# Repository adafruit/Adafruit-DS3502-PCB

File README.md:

## Adafruit DS3502 I2C Digital 10K Potentiometer  PCB

<a href="http://www.adafruit.com/products/4286"><br/>
Click here to purchase one from the Adafruit shop</a>

PCB files for the Adafruit DS3502 I2C Digital 10K Potentiometer . 

Format is EagleCAD schematic and board layout
* https://www.adafruit.com/product/4286

### Description

If you're a person like me that gets exhausted turning knobs all day, the DS3502 is just the ticket to calm all your knob-turning related troubles. Instead of having to _turn knobs_ with your _HANDS_ like an _ANIMAL_ the DS3502 I2C Digital Potentiometer allows you to let your microcontroller adjust the resistance for you! Now you can free your hands to spin your fidget spinner or or eat a slice of pizza while you're on the phone. Talking over an I2C bus, your Arduino, CircuitPython board,  or Python powered computer can talk to the DS3502 and tell it to vary its resistance at your beck and call.

Working with the DS3502 is easy as an I2C controllable pie. We've  put it on a breakout PCB with the required support circuitry and [SparkFun qwiic](https://www.sparkfun.com/qwiic) compatible [STEMMA QT](https://learn.adafruit.com/introducing-adafruit-stemma-qt) connectors to allow you to use it with other similarly equipped boards **without needing to solder.** This handy little helper can work with 3.3V or 5V micros, so it's ready to get to work with a range of development boards. The DS3502 is a simple chip that does one thing well and so it's very easy to work with. Wire it up and set the value for the wiper, thats it. [To make things _even easier_ we've gone and written Arduino and CircuitPython/Python 3 drivers to simplify interfacing with your new knob-replacing friend.](https://learn.adafruit.com/ds3502-i2c-potentiometer/)

"OK, this thing sounds great. Give me some details" you say. OK then, here you go: The wiper value is a 7-bit number meaning there are **128** possible levels of resistance to choose, from **0-10K ohms.** You can even set a default value that will be set on power up. The analog voltage controlled can be from **4.5-15.5V**. Additionally you can use the address jumpers or pins to set the I2C address to one of four values, allowing you to have four DS3502s on the same I2C bus.

### License

Adafruit invests time and resources providing this open source design, please support Adafruit and open-source hardware by purchasing products from [Adafruit](https://www.adafruit.com)!

Designed by Kattni Rembor for Adafruit Industries.

Creative Commons Attribution/Share-Alike, all text above must be included in any redistribution. 
See license.txt for additional details.

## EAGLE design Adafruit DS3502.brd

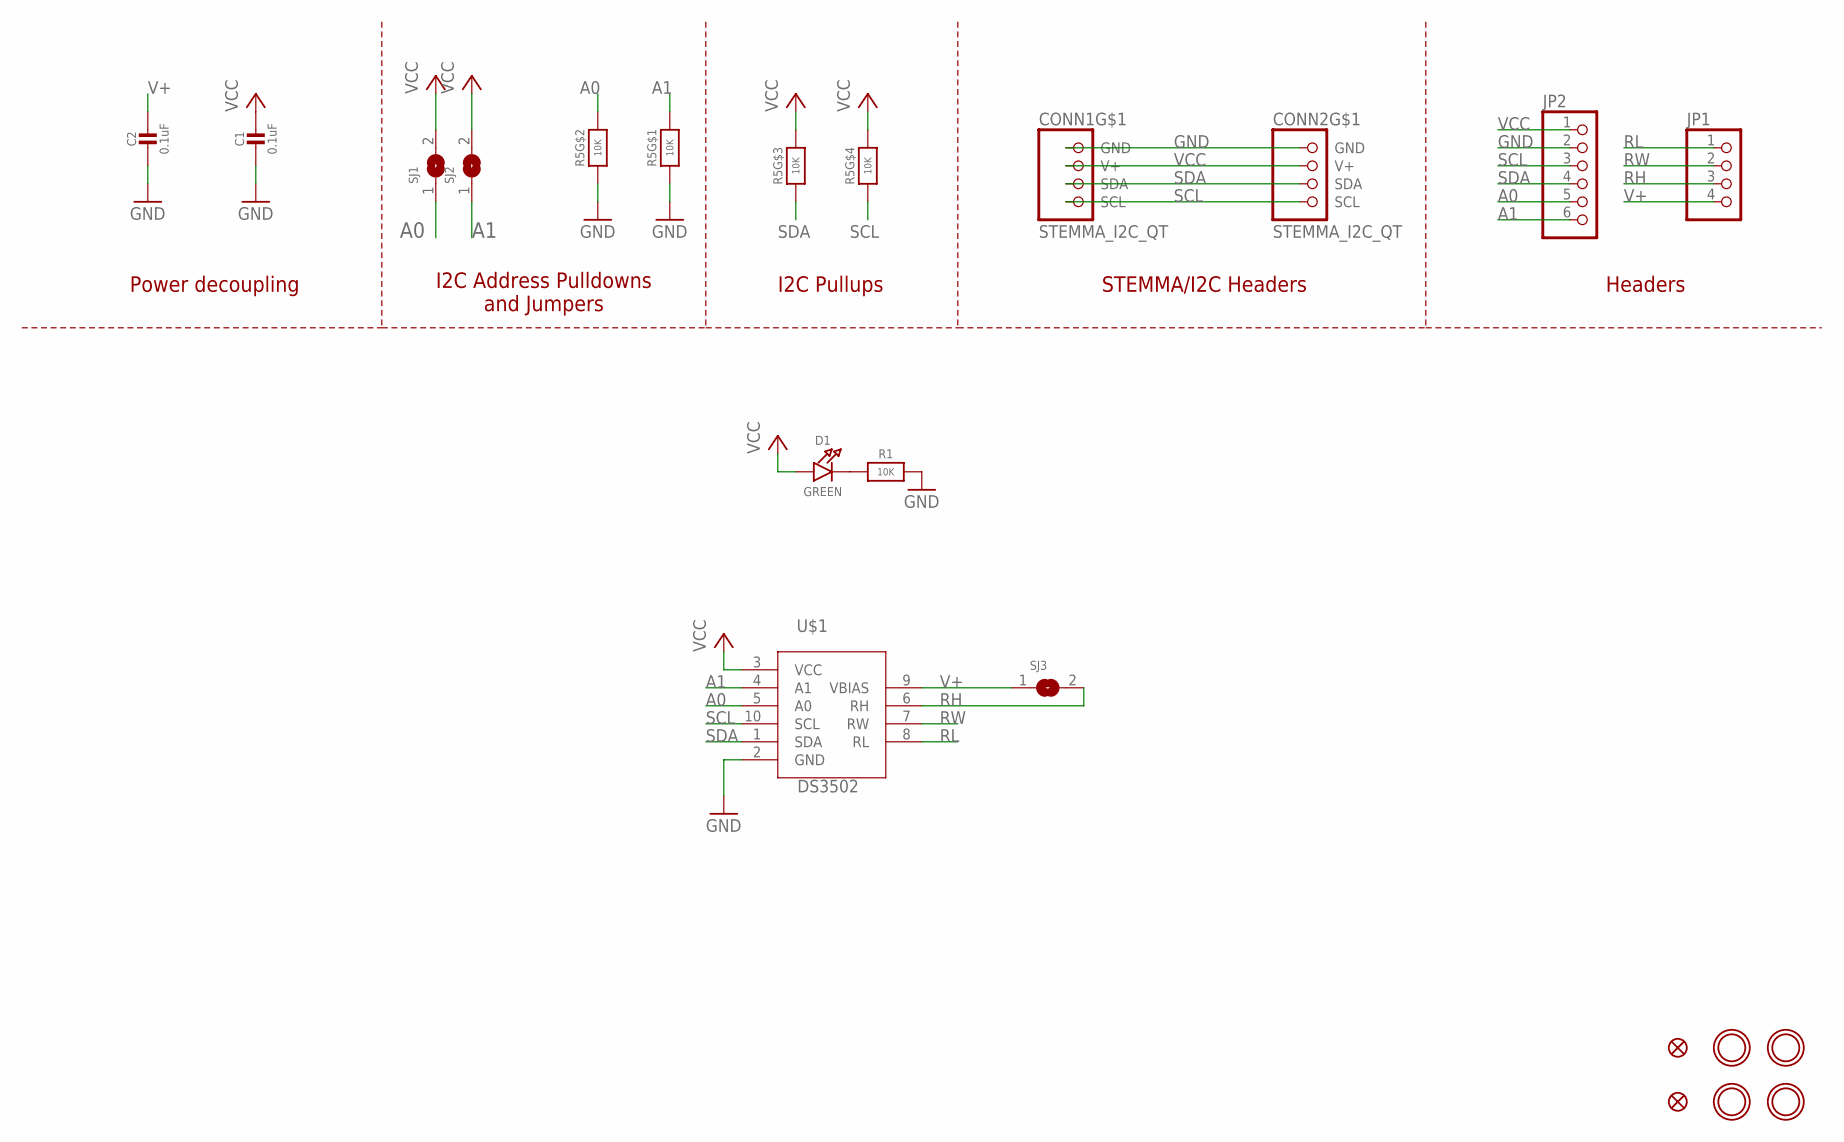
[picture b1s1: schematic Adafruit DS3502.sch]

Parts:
C1, C2: 0.1uF; 0603-NO
CONN1, CONN2: STEMMA_I2C_QT; JST_SH4
D1: GREEN; CHIPLED_0603_NOOUTLINE
FID1, FID2: FIDUCIAL_1MM
JP1: HEADER-1X4ROUND; 1X04_ROUND
JP2: HEADER-1X6ROUND; 1X06_ROUND
R1: 10K; 0603-NO
R5: 10K; RESPACK_4X0603
SJ1, SJ2: SOLDERJUMPER; SOLDERJUMPER_ARROW_NOPASTE
SJ3: SOLDERJUMPERCLOSED; SOLDERJUMPER_CLOSEDWIRE
U$1: DS3502; MSOP10
U$2, U$3, U$6, U$7: MOUNTINGHOLE2.5; MOUNTINGHOLE_2.5_PLATED

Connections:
A0: JP2.5, R5.7 (2), SJ1.1, U$1.5 (A0)
A1: JP2.6, R5.8 (2), SJ2.1, U$1.4 (A1)
GND: C1.2, C2.2, CONN1.1 (GND), CONN2.1 (GND), JP2.2, R1.2, R5.1, R5.2 (1), U$1.2 (GND)
unnamed: D1.C, R1.1
RH: JP1.3, SJ3.2, U$1.6 (RH)
RL: JP1.1, U$1.8 (RL)
RW: JP1.2, U$1.7 (RW)
SCL: CONN1.4 (SCL), CONN2.4 (SCL), JP2.3, R5.4 (1), U$1.10 (SCL)
SDA: CONN1.3 (SDA), CONN2.3 (SDA), JP2.4, R5.3 (1), U$1.1 (SDA)
V+: C2.1, JP1.4, SJ3.1, U$1.9 (VBIAS)
VCC: C1.1, CONN1.2 (V+), CONN2.2 (V+), D1.A, JP2.1, R5.5 (2), R5.6 (2), SJ1.2, SJ2.2, U$1.3 (VCC)

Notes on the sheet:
I2C Address Pulldowns and Jumpers
Power decoupling
I2C Pullups
STEMMA/I2C Headers
Headers

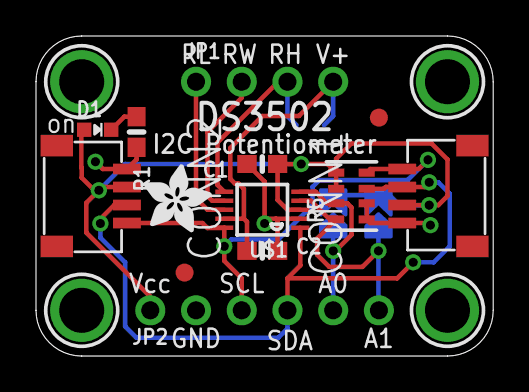
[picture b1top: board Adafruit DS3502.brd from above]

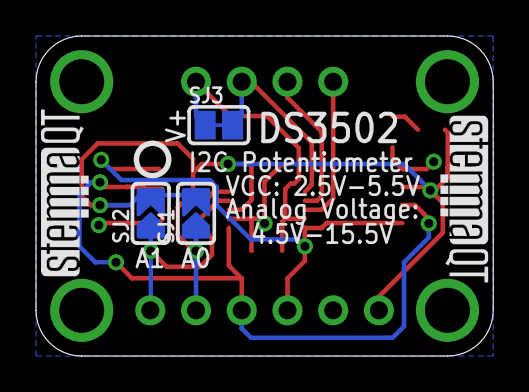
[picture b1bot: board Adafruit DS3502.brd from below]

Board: 2 copper layers, 25.4 x 17.8 mm, 24 parts (7 on the bottom side), 11 nets.

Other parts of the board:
U$5: KATTNI_STOP
U$8: ADAFRUIT_3.5MM
U$9: PCBFEAT-REV-040
U$10, U$11: STEMMAQT

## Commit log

2019-08-05 updated product copy

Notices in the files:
parts and their libraries:
microbuilder: This work is placed in the public domain, and may be freely used for commercial and non-commercial work with the following conditions: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
